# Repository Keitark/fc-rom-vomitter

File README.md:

# FC ROM Vomitter

[日本語](README_JA.md) · [Schematic PDF](docs/nescart-fc-schematic.pdf) · [Manufacturing release](manufacturing/rev-a-fc/)

**Upload an NROM homebrew ROM from a phone, load it into SRAM, and run it on a Japanese Famicom.** No EPROM programmer, cartridge swapping, or battery-backed memory.

The native 60-pin Famicom Rev A-FC is the primary design. A frozen 72-pin NES-001 predecessor is preserved under [`experimental/nes/`](experimental/nes/) for comparison and further development; it is not part of the FC manufacturing release. A separately isolated [ESP32-S3 two-bank Mapper-3 experiment](experimental/mapper3-esp32/) records the post-release bodge wiring, firmware, tests, and limited bench evidence without changing the stable NROM release.

## AI Expo: real hardware → reusable skills

**AIと実機を作る。その経験を、次の設計で使えるスキルにする。**
Build real hardware with AI—and reuse what the engineering process teaches us.

ROM Vomitter's engineering experience helped develop
[PCBA Design Skills](https://github.com/Keitark/pcba-design-skills).
The [ChatPCBA agent plugin](https://github.com/Keitark/chatpcba) packages eleven
specialist skills into an evidence-gated workflow for Codex. The original
cartridge predates the complete local ChatPCBA dashboard; it was not produced
by today's dashboard end to end.

実機開発の経験を再利用可能なスキルへ整理し、ChatPCBAで工程としてつなぎます。
公開物は実機資料・スキル・エージェントプラグインです。展示用ダッシュボードは
別のローカル実装であり、公開ホスティングサービスではありません。

Workflow: interview → requirements and applicable checks → circuit and sourcing
→ readable schematic → applicable simulation → placement/routing → fabrication
package → JLCPCB review. Engineering gates and human order/payment approval
remain distinct. See the validation limits below; a photograph is not a complete
bench qualification report.

## Actual board views

| Component / parts side | Artwork side |
|---|---|
|  |  |

> [!WARNING]
> Rev A-FC has a fabrication-complete design and build-tested firmware, but the assembled hardware has not completed bench validation. Do not insert an untested board into a Famicom. The 10 mm taller PCB also needs a custom shell; original cartridge-shell compatibility is not claimed.

## What it does

1. The ESP32-S3 creates a Wi-Fi access point and browser upload page.
2. An uploaded mapper-0 `.nes` image is CRC-checked and committed to one of two flash slots.
3. At power-up, the ESP32 isolates the console bus, copies PRG and CHR data into SRAM, and verifies every byte.
4. The bus changes to RUN ownership and the blue LED becomes solid.
5. Press the **Famicom console's red RESET button** to start the game.

For bench and unattended workflows, the firmware also supports [USB-C direct
upload and optional HTTPS cloud polling](docs/rom-delivery.md). All delivery
modes use the same validated atomic flash and SRAM-loading path.

Unlike the front-loader NES, the Famicom has no CIC lockout circuit. The cartridge therefore cannot automatically hold and release console reset; the explicit RESET press is part of the Rev A-FC user flow.

```mermaid
flowchart LR
    phone["Phone / laptop"] -->|"Wi-Fi upload"| esp["ESP32-S3"]
    esp --> flash["Two atomic flash slots"]
    flash -->|"CRC-verified copy"| sram["PRG + CHR SRAM"]
    esp -->|"LOAD / RUN ownership"| buffers["74LVC bus isolation"]
    sram --> buffers --> edge["60-pin Famicom edge"]
    edge --> console["Famicom CPU + PPU"]
    reset["Press console RESET"] -.-> console
```

## Hardware at a glance

| Area | Rev A-FC |
|---|---|
| Console | Japanese Famicom 60-pin cartridge slot |
| Supported image | iNES mapper 0 / NROM, 16 or 32 KiB PRG, 8 KiB CHR |
| Loader | ESP32-S3-WROOM-1-N8, SoftAP + browser upload |
| Game storage | Two atomic slots in ESP32 flash |
| Console memory | Two CY62128 128K × 8 SRAMs |
| Bus safety | 74LVC245 isolation with fail-safe LOAD/RUN defaults |
| PCB | 6 layers, 90.0 × 66.8 mm envelope, 1.2 mm, 60 gold fingers |
| Audio | Famicom sound loop through fitted 0 Ω R20 |
| Power/debug | Console 5 V plus USB-C bench power and native USB flashing |

The board keeps the standard-width tongue, connector datum, notches, centre slot, and 1.2 mm mating thickness. Only the edge opposite the fingers is extended by 10 mm for routing space.

## Project status

| Gate | Status | Evidence |
|---|---|---|
| Schematic ERC | **PASS** — 0 errors, 8 reviewed warnings | [`erc.json`](manufacturing/rev-a-fc/evidence/erc.json) |
| PCB connectivity | **PASS** — 0 raw opens | [`drc-classified.json`](manufacturing/rev-a-fc/evidence/drc-classified.json) |
| Classified DRC | **PASS** — 0 real errors | [`drc-classified.json`](manufacturing/rev-a-fc/evidence/drc-classified.json) |
| Layout policy | **PASS** — 0 failures | [`layout-check.txt`](manufacturing/rev-a-fc/evidence/layout-check.txt) |
| CPL registration | **PASS** — 79 fitted references, 0 unresolved | [`cpl-audit.txt`](manufacturing/rev-a-fc/evidence/cpl-audit.txt) |
| Firmware host tests/build | **PASS in preparation; continuously checked by CI** | [workflow](.github/workflows/validate.yml) |
| Electrical/mechanical bench validation | **PENDING** | [bring-up checklist](docs/bring-up.md) |

“0 opens” is not treated as completion by itself. The release also requires classified DRC, power continuity, reference-plane checks, silkscreen review, CPL registration, and visual inspection.

## Quick start for developers

### Firmware

Install [PlatformIO](https://platformio.org/), then:

```powershell
cd firmware
pio run -e esp32-s3
```

Host-test the iNES parser, CRC, and atomic-slot selection:

```powershell
cmake -S host_tests -B host_tests/build
cmake --build host_tests/build --config Release
ctest --test-dir host_tests/build -C Release --output-on-failure
```

The default development access-point password is `vomit-roms`. Change it through menuconfig before using the cartridge in a shared or public environment.

### Hardware

Open [`hardware/nescart-fc.kicad_pro`](hardware/nescart-fc.kicad_pro) in KiCad 10. The checked-in PCB is the exact revision used to create the public manufacturing package.

The schematic is generator-backed:

```powershell
python hardware/tools/gen_sch.py
```

Edit the netlist tables in `gen_sch.py`; do not hand-edit generated connectivity in the `.kicad_sch` files. See [hardware/README.md](hardware/README.md) before regenerating anything.

## Manufacturing release

[`manufacturing/rev-a-fc/`](manufacturing/rev-a-fc/) contains:

- revision-locked Gerber + drill ZIP;
- engineering and JLCPCB-format BOM/CPL files;
- CPL registration audit and assembly drawing;
- DRC/ERC/layout/silkscreen evidence;
- top and bottom manufacturing views and paste-stencil preview;
- a SHA-256 manifest checked in CI.

These files are published for review and reproducibility, **not as a recommendation to order an unvalidated board unchanged**. Read [manufacturing notes](docs/manufacturing.md) and the [bench bring-up gate](docs/bring-up.md) first.

## Experimental NES variant

[`experimental/nes/`](experimental/nes/) preserves the earlier 72-pin front-loader NES-001 design. It uses an ATtiny CIC clone to hold the console in reset while the ESP32 loads SRAM, which is materially different from the manual-reset FC flow. The snapshot passed its recorded schematic and PCB checks, but its assembly-placement gate and hardware validation are incomplete, so it is intentionally **not fabrication-ready**.

## Experimental Mapper 3 modification

[`experimental/mapper3-esp32/`](experimental/mapper3-esp32/) documents an
ESP32-S3-only, two-bank CNROM modification applied to one assembled Rev A-FC
board. It adds no new processor: a core-1 IRAM polling loop observes CPU D0 and
the existing decoded control signals, then drives CHR SRAM A13 through GPIO36.

Host tests, the ESP32 build, Mapper-0 regression, and one two-bank Mapper-3
target passed their recorded checks. Electrical margin, worst-case timing,
long-run Wi-Fi stress, and multi-board repeatability remain `USER_REVIEW`.
This is a reproducible experiment, not a revised manufacturing release.

## Repository map

```text
hardware/                 KiCad 10 release source, libraries, models and core generators
firmware/                 ESP-IDF / PlatformIO loader firmware and host tests
manufacturing/rev-a-fc/   sanitized Gerber, BOM, CPL, evidence and hashes
experimental/nes/          frozen 72-pin NES-001 design snapshot (not released)
experimental/mapper3-esp32/ post-release two-bank CNROM bodge and firmware
docs/                     architecture, bring-up, manufacturing and licensing notes
scripts/                  repository and release-integrity checks
```

## Documentation

- [Architecture and safety invariants](docs/architecture.md)
- [First-board bring-up](docs/bring-up.md)
- [Browser, USB-C and cloud ROM delivery](docs/rom-delivery.md)
- [Manufacturing and release interpretation](docs/manufacturing.md)
- [FC60 pin map](hardware/docs/pinout-fc.md)
- [Layout and electrical guidance](hardware/docs/layout-electrical-guidance.md)
- [Licensing and attribution](docs/licensing.md)
- [Japanese README / 日本語](README_JA.md)
- [Experimental ESP32-S3 Mapper 3 modification](experimental/mapper3-esp32/)

## License and credits

This is a dual-licensed repository. Software and original general documentation are MIT. KiCad hardware design files, manufacturing artifacts, and designated visual/model assets are CC BY-SA 4.0; see [the exact scope and attributions](docs/licensing.md).

Connector behavior and dimensional research reference the community-maintained [NESdev Wiki](https://www.nesdev.org/wiki/Cartridge_connector) and the [NES/Famicom cartridge dimensions project](https://github.com/Gumball2415/NES-Famicom-Cartridge-Dimensions). The SRAM STEP model is from KiCad Packages3D and retains its upstream license and exception.

Famicom and Nintendo are trademarks of Nintendo. This independent project is not affiliated with or endorsed by Nintendo. Use homebrew software you have the right to run.

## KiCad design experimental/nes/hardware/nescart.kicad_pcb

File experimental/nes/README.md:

# Experimental 72-pin NES-001 variant

[日本語](#日本語) · [Schematic PDF](docs/nescart-schematic.pdf)

This directory preserves the earlier front-loader NES-001 design as an experimental snapshot. It is included to make the architectural differences and design history reviewable; it is **not part of the Rev A-FC manufacturing release**.

## Why it differs from the Famicom board

The NES-001 contains a CIC lockout circuit. An ATtiny13A running a CIC-clone firmware keeps the console in reset while the ESP32-S3 owns the cartridge SRAM bus, then permits boot only after the ROM image has been copied and verified.

```mermaid
flowchart LR
    phone["Phone / laptop"] -->|"Wi-Fi upload"| esp["ESP32-S3"]
    esp -->|"load + verify"| sram["PRG + CHR SRAM"]
    cic["ATtiny13A CIC clone"] -->|"hold console reset"| nes["NES-001"]
    esp -->|"LOAD / RUN"| buffers["Bus isolation"]
    sram --> buffers --> edge["72-pin edge"] --> nes
```

## Frozen snapshot status

| Item | Recorded state |
|---|---|
| Target | Front-loader NES-001, 72-pin, NROM |
| PCB | 6 layers, 1.2 mm, CY62128 SRAM variant |
| ERC | 0 errors, 8 reviewed warnings |
| Raw disconnects | 0 |
| Classified DRC | 0 real errors |
| Layout policy | 0 failures |
| Assembly placement | **Incomplete** — browser-only placement edits existed and a clean regenerated CPL review was still required |
| Bench validation | **Not completed** |

The snapshot also records accepted prototype USB risks: 2.63 mm D+/D− length skew, one-via asymmetry, and no connector-side ESD device. Re-audit those choices before deriving hardware from this version.

The exact source hashes are recorded in [`evidence/snapshot.json`](evidence/snapshot.json). No Gerber/BOM/CPL manufacturing bundle is published for this experimental variant.

## License and attribution

The KiCad source, renders, and evidence in this directory are CC BY-SA 4.0. The cartridge edge footprint and board geometry derive from [emeargt/nes-cnrom](https://github.com/emeargt/nes-cnrom). See the repository [licensing details](../../docs/licensing.md).

## 日本語

ここにはフロントローダーNES-001用72ピン版の設計スナップショットを、実験資料として保存しています。ATtiny13AのCICクローンで本体をリセット状態に保ち、その間にESP32-S3がSRAMへROMを書き込む構成です。

回路図・未接続・分類済みDRC・レイアウト検査は記録上PASSですが、JLCPCB上の部品位置確認でブラウザ内だけの補正が残っており、元CPLへ反映して再生成・再アップロードする最終ゲートが未完了でした。実機検証も未完了です。このため、FC版とは分離し、**そのまま製造するためのリリースではありません**。

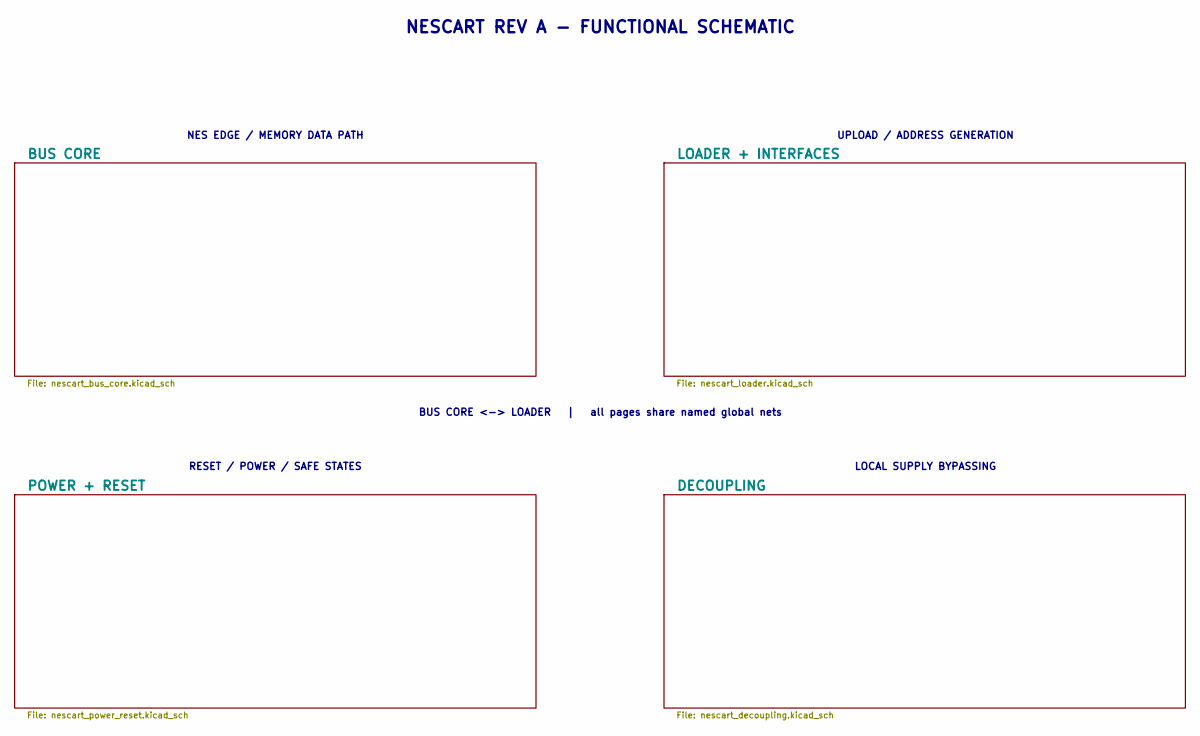
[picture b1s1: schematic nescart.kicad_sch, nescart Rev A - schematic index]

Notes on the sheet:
NESCART REV A - FUNCTIONAL SCHEMATIC
NES EDGE / MEMORY DATA PATH
UPLOAD / ADDRESS GENERATION
RESET / POWER / SAFE STATES
LOCAL SUPPLY BYPASSING
BUS CORE <-> LOADER | all pages share named global nets

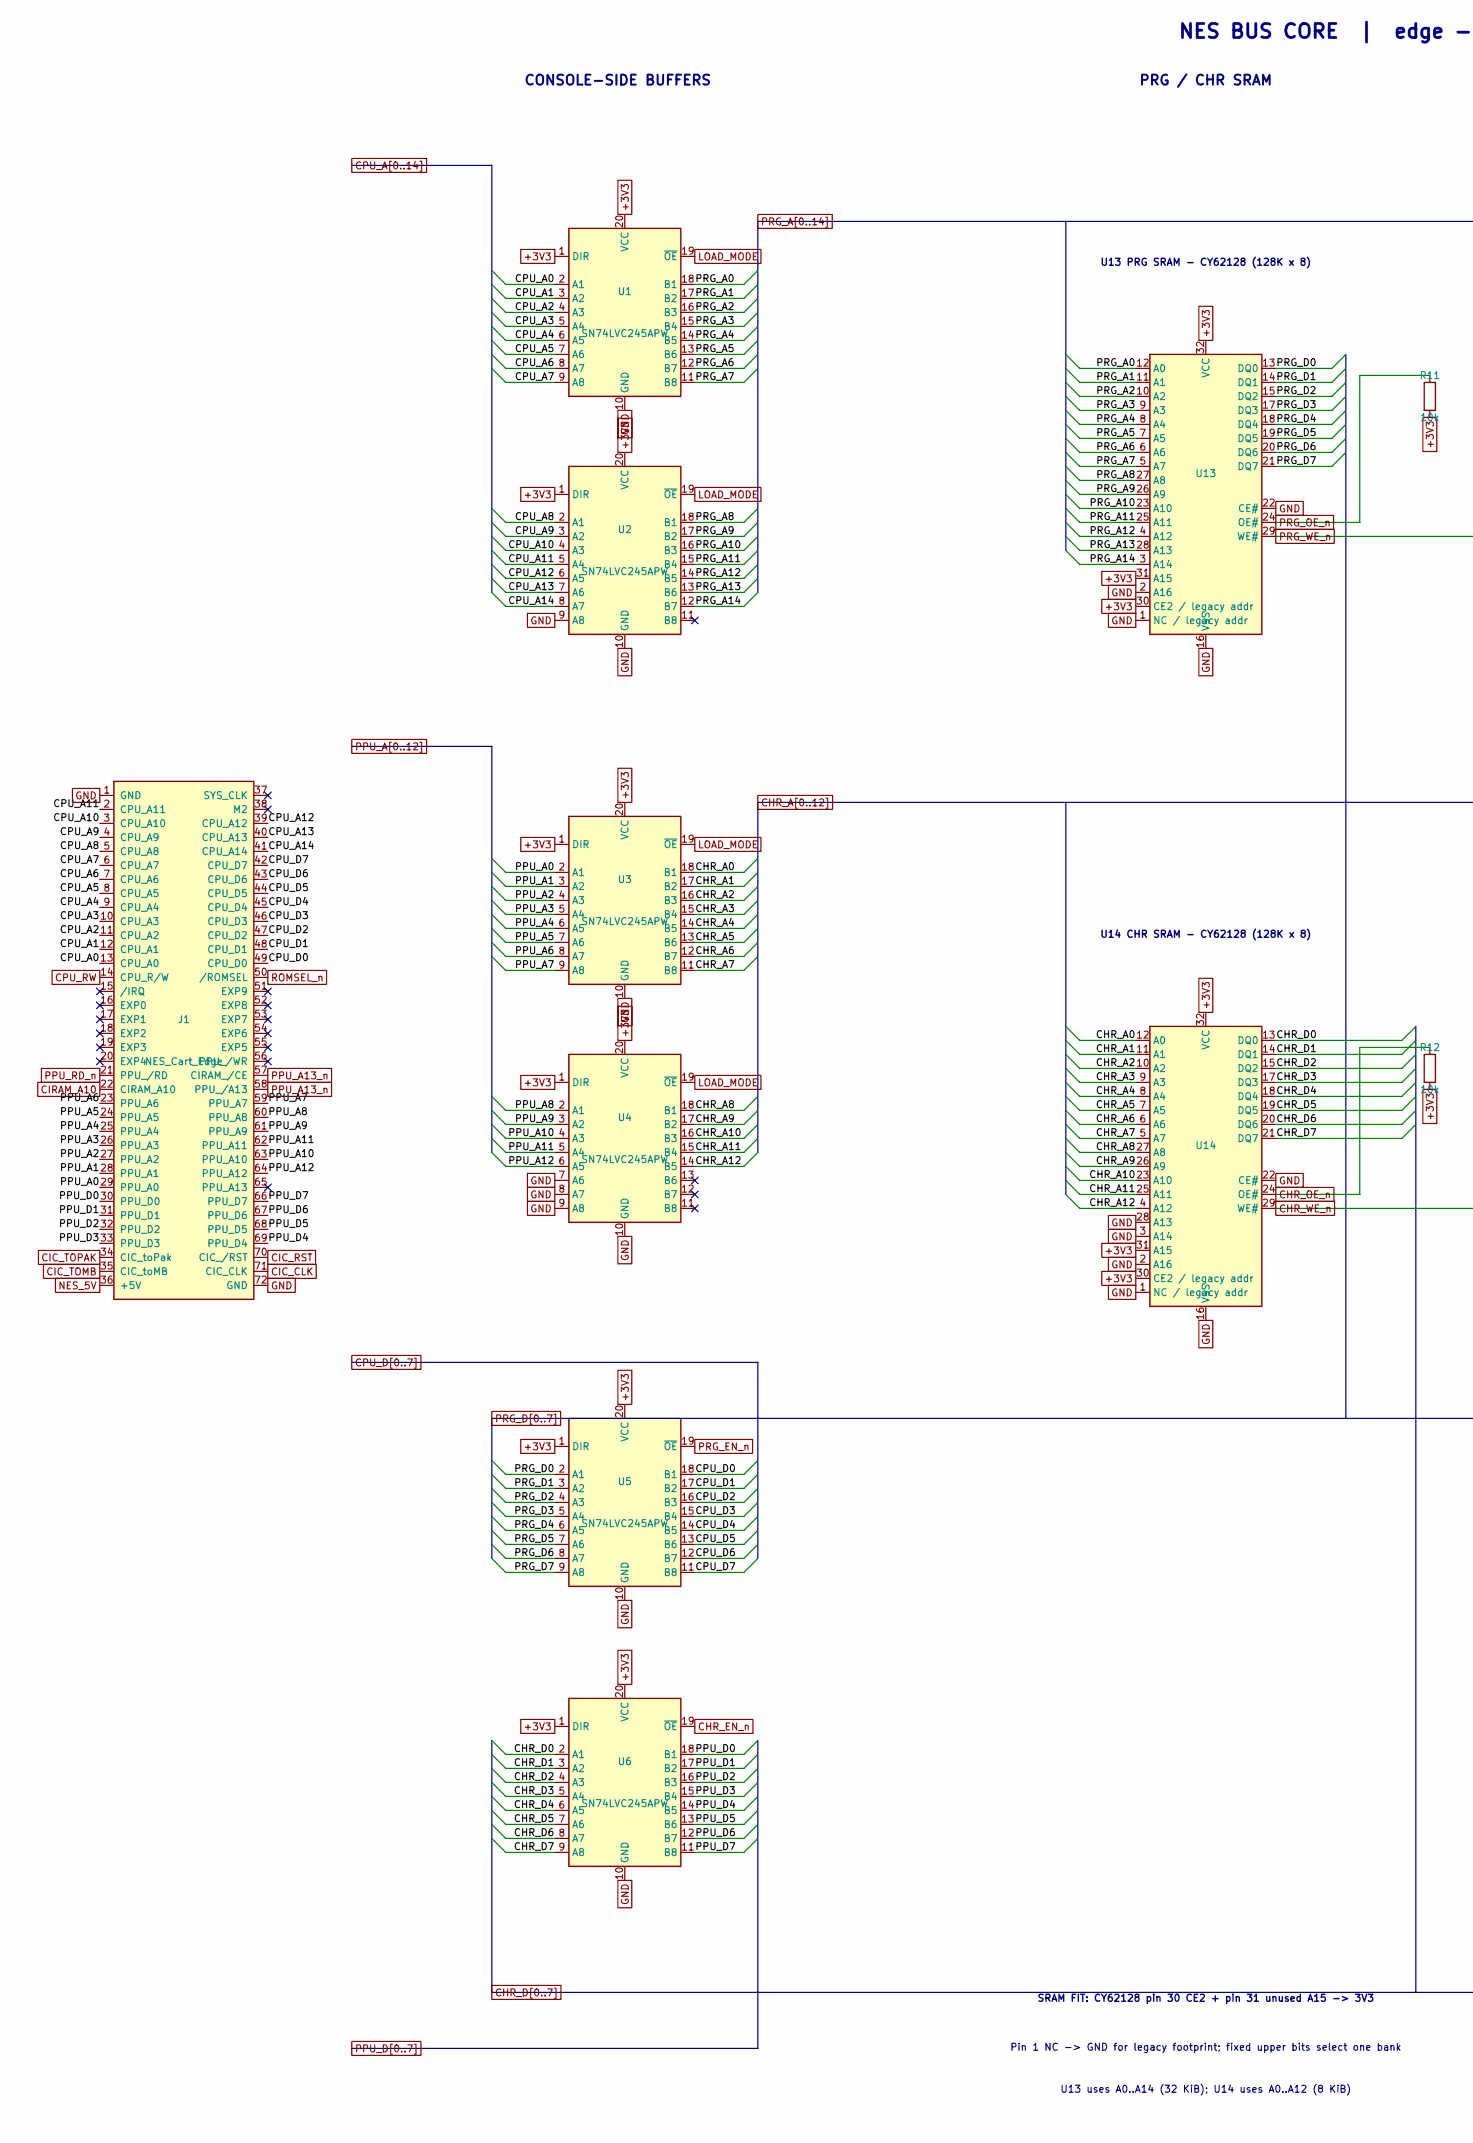
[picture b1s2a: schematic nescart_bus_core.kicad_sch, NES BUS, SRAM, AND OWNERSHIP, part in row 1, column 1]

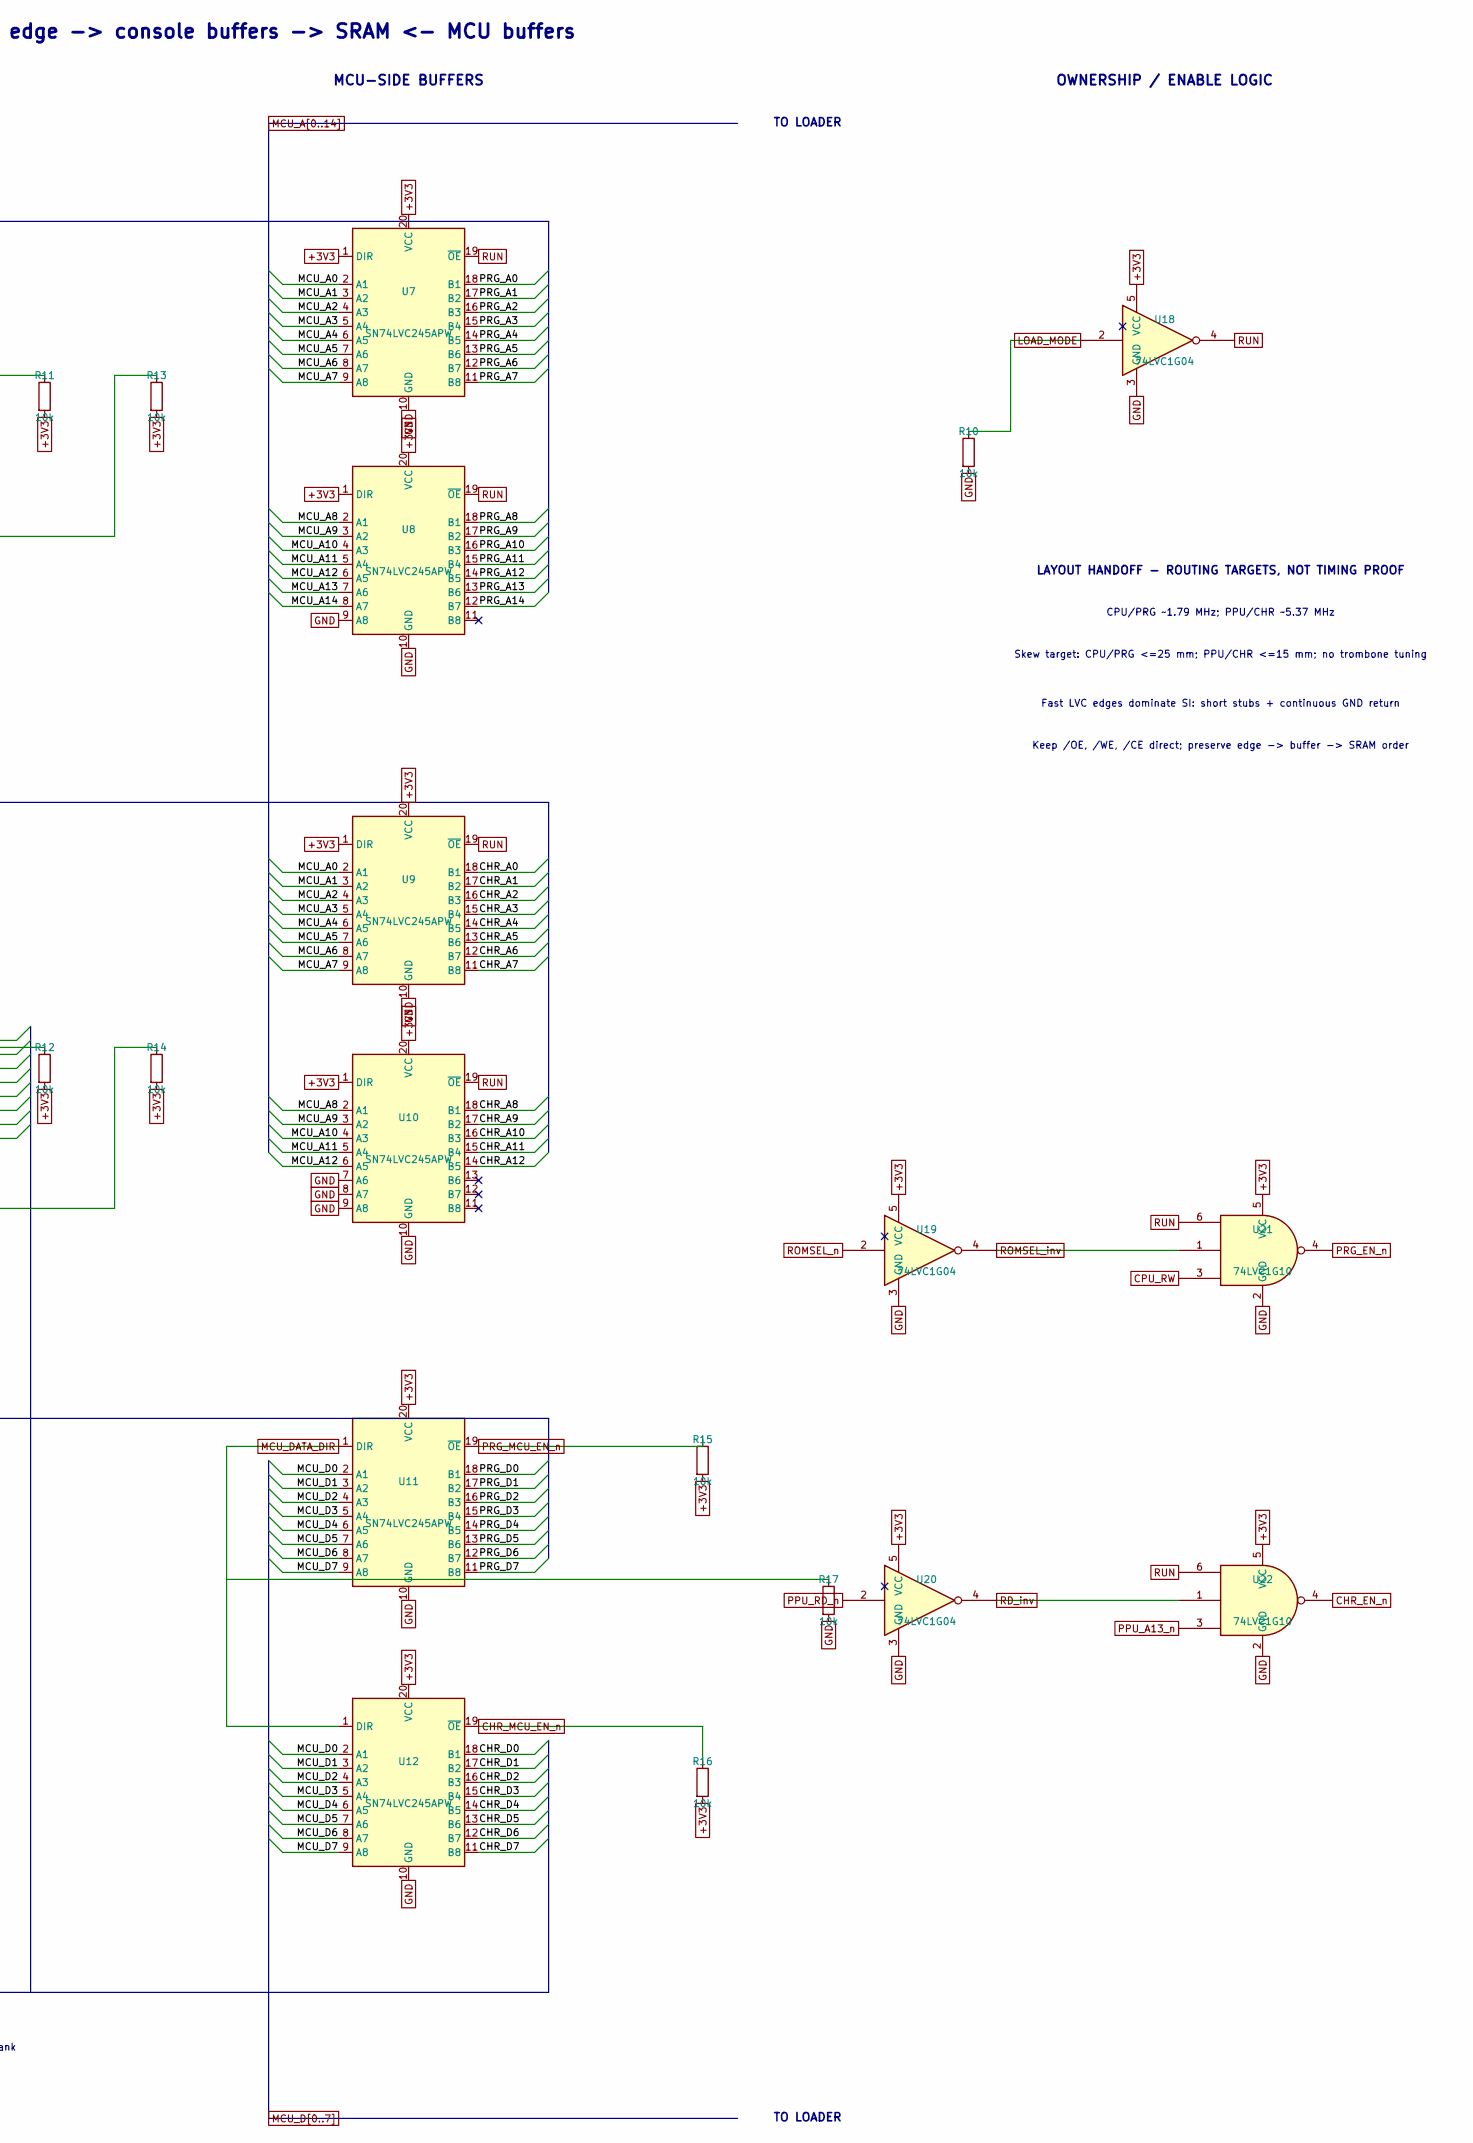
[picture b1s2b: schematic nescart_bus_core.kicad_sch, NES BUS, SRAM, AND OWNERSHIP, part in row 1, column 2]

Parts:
J1: NES_Cart_Edge; cartridge_edge_72
R10, R11, R12, R13, R14, R15, R16, R17: 10k; R_0603_1608Metric; MPN 0603 10k 1%
U1, U2, U3, U4, U5, U6, U7, U8, U9, U10, U11, U12: SN74LVC245APW; TSSOP-20_4.4x6.5mm_P0.65mm; MPN SN74LVC245APWR
U13, U14: CY62128EV30; SOP-32_11.305x20.495mm_P1.27mm; MPN CY62128EV30LL-45SXIT; LCSC C2840304
U18, U19, U20: 74LVC1G04; SOT-353_SC-70-5; MPN SN74LVC1G04DCKR
U21, U22: 74LVC1G10; SOT-363_SC-70-6; MPN SN74LVC1G10DCKR

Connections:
CHR_A0: U3.18 (B1), U9.18 (B1), U14.12 (A0)
CHR_A1: U3.17 (B2), U9.17 (B2), U14.11 (A1)
CHR_A2: U3.16 (B3), U9.16 (B3), U14.10 (A2)
CHR_A3: U3.15 (B4), U9.15 (B4), U14.9 (A3)
CHR_A4: U3.14 (B5), U9.14 (B5), U14.8 (A4)
CHR_A5: U3.13 (B6), U9.13 (B6), U14.7 (A5)
CHR_A6: U3.12 (B7), U9.12 (B7), U14.6 (A6)
CHR_A7: U3.11 (B8), U9.11 (B8), U14.5 (A7)
CHR_A8: U4.18 (B1), U10.18 (B1), U14.27 (A8)
CHR_A9: U4.17 (B2), U10.17 (B2), U14.26 (A9)
CHR_A10: U4.16 (B3), U10.16 (B3), U14.23 (A10)
CHR_A11: U4.15 (B4), U10.15 (B4), U14.25 (A11)
CHR_A12: U4.14 (B5), U10.14 (B5), U14.4 (A12)
CHR_D0: U6.2 (A1), U12.18 (B1), U14.13 (DQ0)
CHR_D1: U6.3 (A2), U12.17 (B2), U14.14 (DQ1)
CHR_D2: U6.4 (A3), U12.16 (B3), U14.15 (DQ2)
CHR_D3: U6.5 (A4), U12.15 (B4), U14.17 (DQ3)
CHR_D4: U6.6 (A5), U12.14 (B5), U14.18 (DQ4)
CHR_D5: U6.7 (A6), U12.13 (B6), U14.19 (DQ5)
CHR_D6: U6.8 (A7), U12.12 (B7), U14.20 (DQ6)
CHR_D7: U6.9 (A8), U12.11 (B8), U14.21 (DQ7)
CHR_EN_n: U6.19 (~OE), U22.4
CHR_MCU_EN_n: R16.1, U12.19 (~OE); also elsewhere on the board
CHR_OE_n: R12.1, U14.24 (OE#); also elsewhere on the board
CHR_WE_n: R14.1, U14.29 (WE#); also elsewhere on the board
CIC_CLK: J1.71 (CIC_CLK); also elsewhere on the board
CIC_RST: J1.70 (CIC_/RST); also elsewhere on the board
CIC_TOMB: J1.35 (CIC_toMB); also elsewhere on the board
CIC_TOPAK: J1.34 (CIC_toPak); also elsewhere on the board
CIRAM_A10: J1.22 (CIRAM_A10); also elsewhere on the board
CPU_A0: J1.13 (CPU_A0), U1.2 (A1)
CPU_A1: J1.12 (CPU_A1), U1.3 (A2)
CPU_A2: J1.11 (CPU_A2), U1.4 (A3)
CPU_A3: J1.10 (CPU_A3), U1.5 (A4)
CPU_A4: J1.9 (CPU_A4), U1.6 (A5)
CPU_A5: J1.8 (CPU_A5), U1.7 (A6)
CPU_A6: J1.7 (CPU_A6), U1.8 (A7)
CPU_A7: J1.6 (CPU_A7), U1.9 (A8)
CPU_A8: J1.5 (CPU_A8), U2.2 (A1)
CPU_A9: J1.4 (CPU_A9), U2.3 (A2)
CPU_A10: J1.3 (CPU_A10), U2.4 (A3)
CPU_A11: J1.2 (CPU_A11), U2.5 (A4)
CPU_A12: J1.39 (CPU_A12), U2.6 (A5)
CPU_A13: J1.40 (CPU_A13), U2.7 (A6)
CPU_A14: J1.41 (CPU_A14), U2.8 (A7)
CPU_D0: J1.49 (CPU_D0), U5.18 (B1)
CPU_D1: J1.48 (CPU_D1), U5.17 (B2)
CPU_D2: J1.47 (CPU_D2), U5.16 (B3)
CPU_D3: J1.46 (CPU_D3), U5.15 (B4)
CPU_D4: J1.45 (CPU_D4), U5.14 (B5)
CPU_D5: J1.44 (CPU_D5), U5.13 (B6)
CPU_D6: J1.43 (CPU_D6), U5.12 (B7)
CPU_D7: J1.42 (CPU_D7), U5.11 (B8)
CPU_RW: J1.14 (CPU_R/W), U21.3
GND: J1.1 (GND), J1.72 (GND), R10.2, R17.2, U1.10 (GND), U2.9 (A8), U2.10 (GND), U3.10 (GND), U4.7 (A6), U4.8 (A7), U4.9 (A8), U4.10 (GND), U5.10 (GND), U6.10 (GND), U7.10 (GND), U8.9 (A8), U8.10 (GND), U9.10 (GND), U10.7 (A6), U10.8 (A7), U10.9 (A8), U10.10 (GND), U11.10 (GND), U12.10 (GND), U13.1 (NC / legacy addr), U13.2 (A16), U13.16 (VSS), U13.22 (CE#), U14.1 (NC / legacy addr), U14.2 (A16), U14.3 (A14), U14.16 (VSS), U14.22 (CE#), U14.28 (A13), U18.3 (GND), U19.3 (GND), U20.3 (GND), U21.2 (GND), U22.2 (GND); also elsewhere on the board
LOAD_MODE: R10.1, U1.19 (~OE), U2.19 (~OE), U3.19 (~OE), U4.19 (~OE), U18.2; also elsewhere on the board
MCU_A0: U7.2 (A1), U9.2 (A1); also elsewhere on the board
MCU_A1: U7.3 (A2), U9.3 (A2); also elsewhere on the board
MCU_A2: U7.4 (A3), U9.4 (A3); also elsewhere on the board
MCU_A3: U7.5 (A4), U9.5 (A4); also elsewhere on the board
MCU_A4: U7.6 (A5), U9.6 (A5); also elsewhere on the board
MCU_A5: U7.7 (A6), U9.7 (A6); also elsewhere on the board
MCU_A6: U7.8 (A7), U9.8 (A7); also elsewhere on the board
MCU_A7: U7.9 (A8), U9.9 (A8); also elsewhere on the board
MCU_A8: U8.2 (A1), U10.2 (A1); also elsewhere on the board
MCU_A9: U8.3 (A2), U10.3 (A2); also elsewhere on the board
MCU_A10: U8.4 (A3), U10.4 (A3); also elsewhere on the board
MCU_A11: U8.5 (A4), U10.5 (A4); also elsewhere on the board
MCU_A12: U8.6 (A5), U10.6 (A5); also elsewhere on the board
MCU_A13: U8.7 (A6); also elsewhere on the board
MCU_A14: U8.8 (A7); also elsewhere on the board
MCU_D0: U11.2 (A1), U12.2 (A1); also elsewhere on the board
MCU_D1: U11.3 (A2), U12.3 (A2); also elsewhere on the board
MCU_D2: U11.4 (A3), U12.4 (A3); also elsewhere on the board
MCU_D3: U11.5 (A4), U12.5 (A4); also elsewhere on the board
MCU_D4: U11.6 (A5), U12.6 (A5); also elsewhere on the board
MCU_D5: U11.7 (A6), U12.7 (A6); also elsewhere on the board
MCU_D6: U11.8 (A7), U12.8 (A7); also elsewhere on the board
MCU_D7: U11.9 (A8), U12.9 (A8); also elsewhere on the board
MCU_DATA_DIR: R17.1, U11.1 (DIR), U12.1 (DIR); also elsewhere on the board
NES_5V: J1.36 (+5V); also elsewhere on the board
PPU_A0: J1.29 (PPU_A0), U3.2 (A1)
PPU_A1: J1.28 (PPU_A1), U3.3 (A2)
PPU_A2: J1.27 (PPU_A2), U3.4 (A3)
PPU_A3: J1.26 (PPU_A3), U3.5 (A4)
PPU_A4: J1.25 (PPU_A4), U3.6 (A5)
PPU_A5: J1.24 (PPU_A5), U3.7 (A6)
PPU_A6: J1.23 (PPU_A6), U3.8 (A7)
PPU_A7: J1.59 (PPU_A7), U3.9 (A8)
PPU_A8: J1.60 (PPU_A8), U4.2 (A1)
PPU_A9: J1.61 (PPU_A9), U4.3 (A2)
PPU_A10: J1.63 (PPU_A10), U4.4 (A3); also elsewhere on the board
PPU_A11: J1.62 (PPU_A11), U4.5 (A4); also elsewhere on the board
PPU_A12: J1.64 (PPU_A12), U4.6 (A5)
PPU_A13_n: J1.57 (CIRAM_/CE), J1.58 (PPU_/A13), U22.3
PPU_D0: J1.30 (PPU_D0), U6.18 (B1)
PPU_D1: J1.31 (PPU_D1), U6.17 (B2)
PPU_D2: J1.32 (PPU_D2), U6.16 (B3)
PPU_D3: J1.33 (PPU_D3), U6.15 (B4)
PPU_D4: J1.69 (PPU_D4), U6.14 (B5)
PPU_D5: J1.68 (PPU_D5), U6.13 (B6)
PPU_D6: J1.67 (PPU_D6), U6.12 (B7)
PPU_D7: J1.66 (PPU_D7), U6.11 (B8)
PPU_RD_n: J1.21 (PPU_/RD), U20.2
PRG_A0: U1.18 (B1), U7.18 (B1), U13.12 (A0)
PRG_A1: U1.17 (B2), U7.17 (B2), U13.11 (A1)
PRG_A2: U1.16 (B3), U7.16 (B3), U13.10 (A2)
PRG_A3: U1.15 (B4), U7.15 (B4), U13.9 (A3)
PRG_A4: U1.14 (B5), U7.14 (B5), U13.8 (A4)
PRG_A5: U1.13 (B6), U7.13 (B6), U13.7 (A5)
PRG_A6: U1.12 (B7), U7.12 (B7), U13.6 (A6)
PRG_A7: U1.11 (B8), U7.11 (B8), U13.5 (A7)
PRG_A8: U2.18 (B1), U8.18 (B1), U13.27 (A8)
PRG_A9: U2.17 (B2), U8.17 (B2), U13.26 (A9)
PRG_A10: U2.16 (B3), U8.16 (B3), U13.23 (A10)
PRG_A11: U2.15 (B4), U8.15 (B4), U13.25 (A11)
PRG_A12: U2.14 (B5), U8.14 (B5), U13.4 (A12)
PRG_A13: U2.13 (B6), U8.13 (B6), U13.28 (A13)
PRG_A14: U2.12 (B7), U8.12 (B7), U13.3 (A14)
PRG_D0: U5.2 (A1), U11.18 (B1), U13.13 (DQ0)
PRG_D1: U5.3 (A2), U11.17 (B2), U13.14 (DQ1)
PRG_D2: U5.4 (A3), U11.16 (B3), U13.15 (DQ2)
PRG_D3: U5.5 (A4), U11.15 (B4), U13.17 (DQ3)
PRG_D4: U5.6 (A5), U11.14 (B5), U13.18 (DQ4)
PRG_D5: U5.7 (A6), U11.13 (B6), U13.19 (DQ5)
PRG_D6: U5.8 (A7), U11.12 (B7), U13.20 (DQ6)
PRG_D7: U5.9 (A8), U11.11 (B8), U13.21 (DQ7)
PRG_EN_n: U5.19 (~OE), U21.4
PRG_MCU_EN_n: R15.1, U11.19 (~OE); also elsewhere on the board
PRG_OE_n: R11.1, U13.24 (OE#); also elsewhere on the board
PRG_WE_n: R13.1, U13.29 (WE#); also elsewhere on the board
RD_inv: U20.4, U22.1
ROMSEL_inv: U19.4, U21.1
ROMSEL_n: J1.50 (/ROMSEL), U19.2
RUN: U7.19 (~OE), U8.19 (~OE), U9.19 (~OE), U10.19 (~OE), U18.4, U21.6, U22.6

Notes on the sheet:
NES BUS CORE | edge -> console buffers -> SRAM <- MCU buffers
CONSOLE-SIDE BUFFERS
PRG / CHR SRAM
U13 PRG SRAM - CY62128 (128K x 8)
U14 CHR SRAM - CY62128 (128K x 8)
MCU-SIDE BUFFERS
OWNERSHIP / ENABLE LOGIC
TO LOADER
LAYOUT HANDOFF - ROUTING TARGETS, NOT TIMING PROOF
CPU/PRG ~1.79 MHz; PPU/CHR ~5.37 MHz
Skew target: CPU/PRG <=25 mm; PPU/CHR <=15 mm; no trombone tuning
Fast LVC edges dominate SI: short stubs + continuous GND return
Keep /OE, /WE, /CE direct; preserve edge -> buffer -> SRAM order
SRAM FIT: CY62128 pin 30 CE2 + pin 31 unused A15 -> 3V3
Pin 1 NC -> GND for legacy footprint; fixed upper bits select one bank
U13 uses A0..A14 (32 KiB); U14 uses A0..A12 (8 KiB)

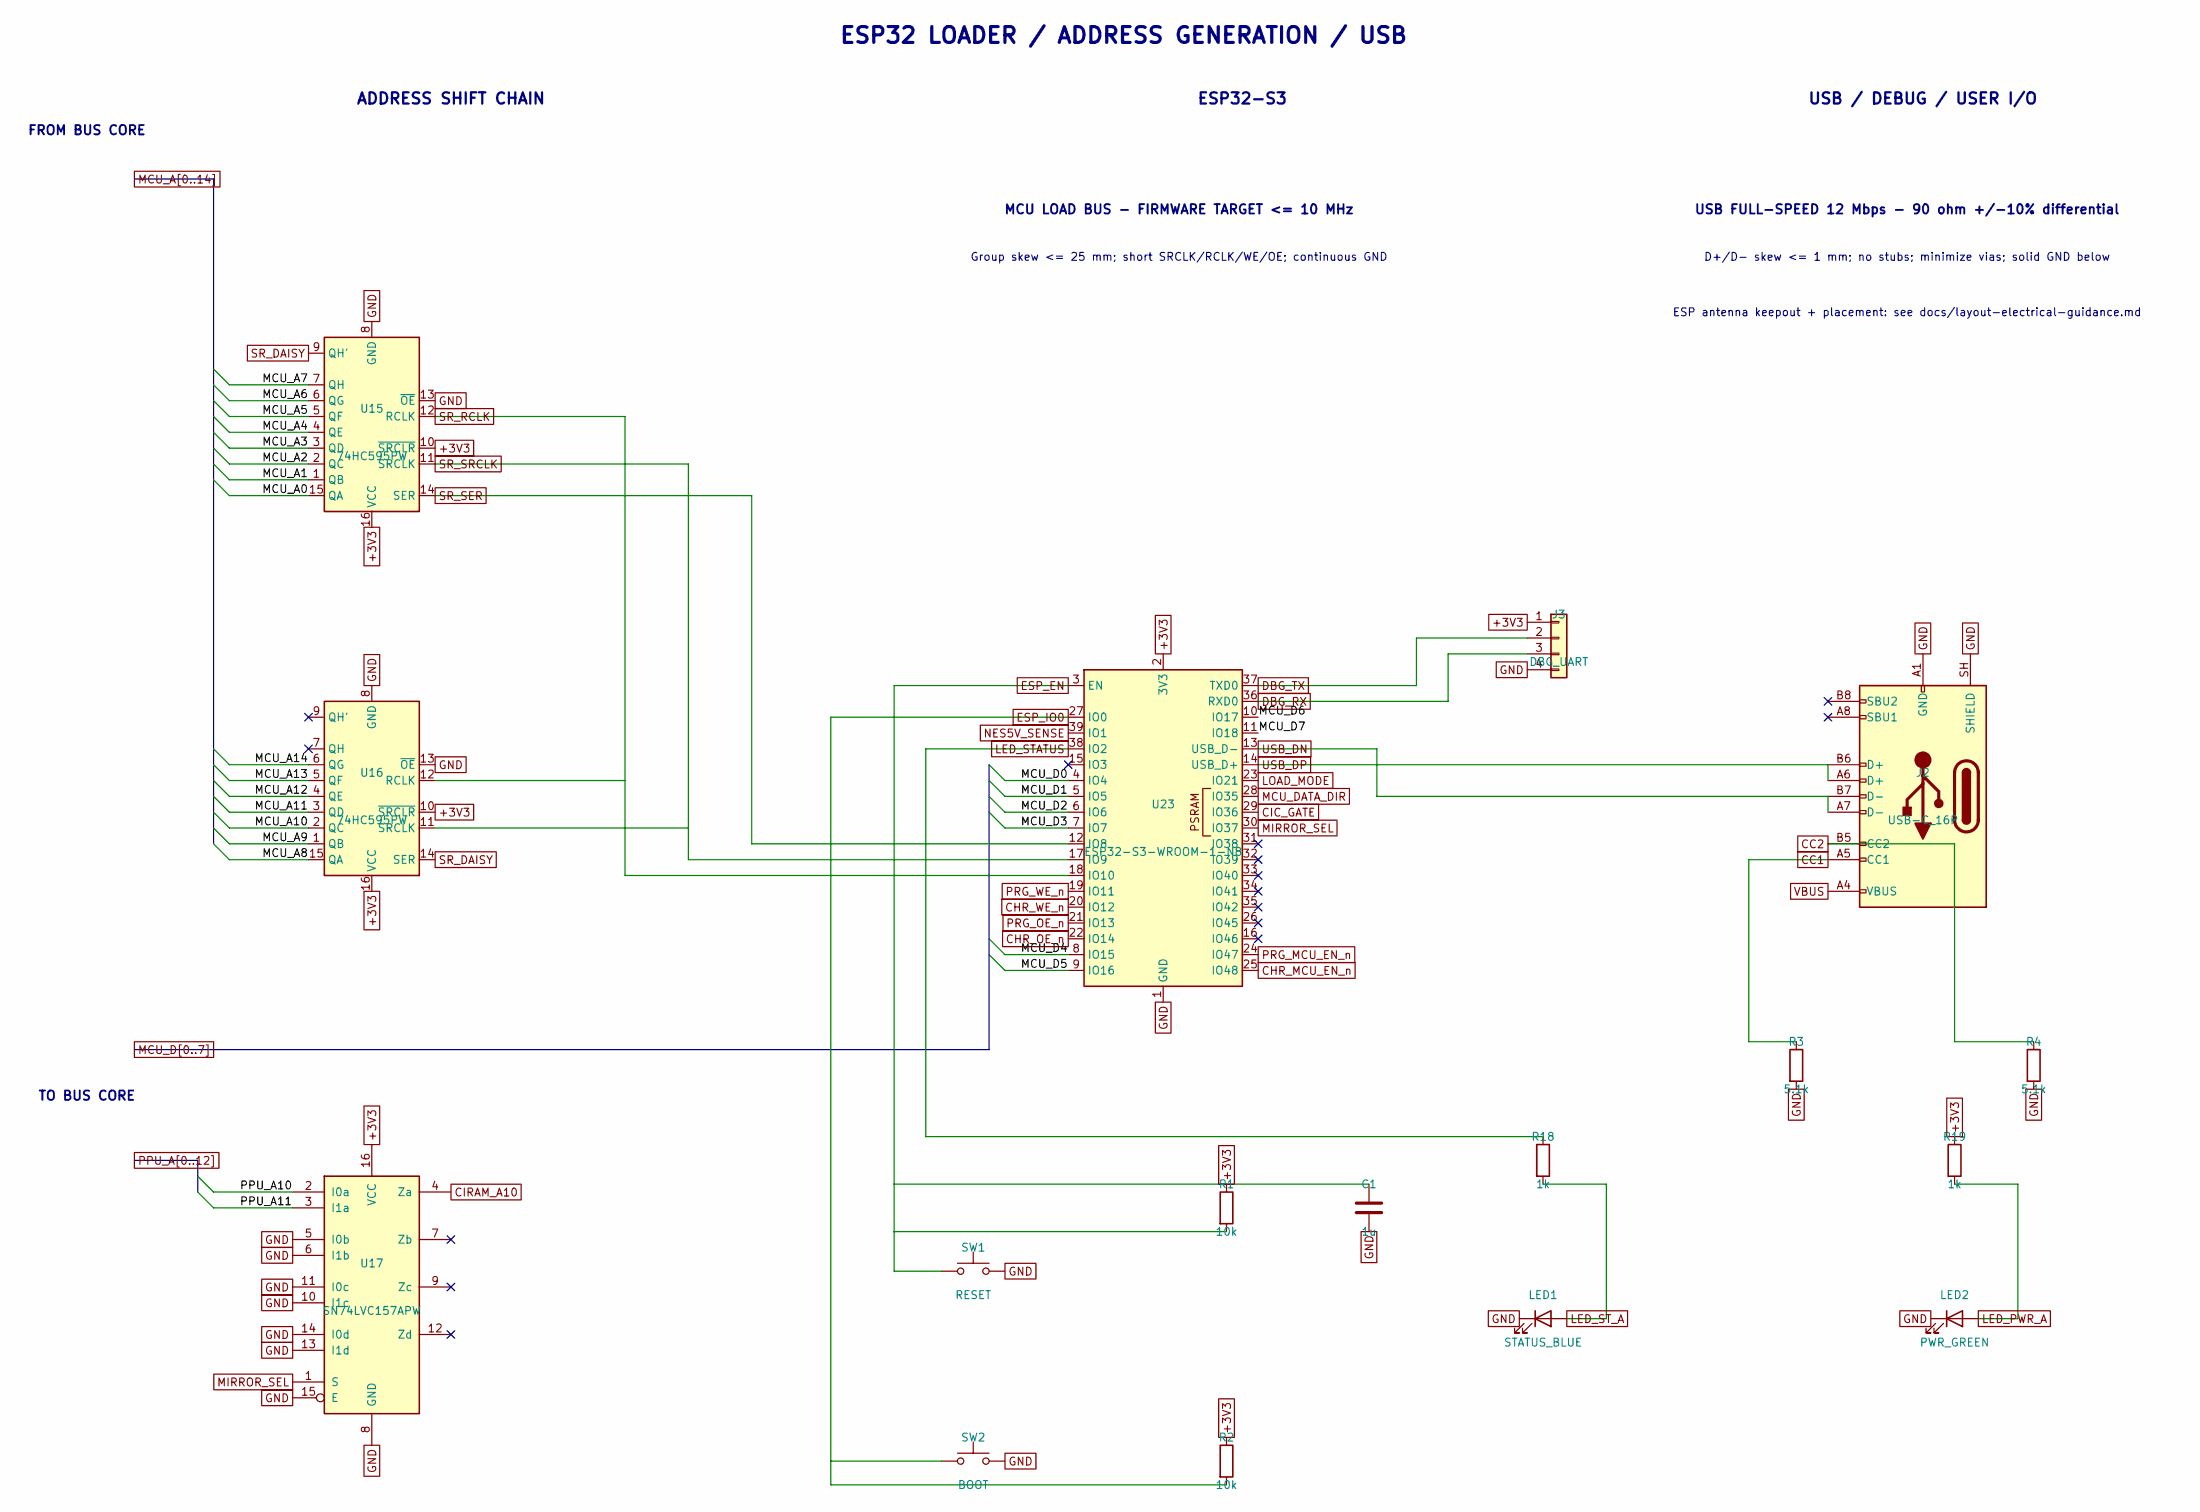
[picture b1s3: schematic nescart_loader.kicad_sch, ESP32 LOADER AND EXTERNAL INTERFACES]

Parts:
C1: 1u; C_0603_1608Metric; MPN 1u X7R
J2: USB-C_16P; USB_C_Receptacle_HRO_TYPE-C-31-M-12; MPN HRO TYPE-C-31-M-12
J3: DBG_UART; PinHeader_1x04_P2.54mm_Vertical; MPN PinHeader 1x4
LED1: STATUS_BLUE; LED_0603_1608Metric; MPN 0603 LED
LED2: PWR_GREEN; LED_0603_1608Metric; MPN 0603 LED
R1, R2: 10k; R_0603_1608Metric; MPN 0603 10k 1%
R3, R4: 5.1k; R_0603_1608Metric; MPN 0603 5.1k 1%
R18, R19: 1k; R_0603_1608Metric; MPN 0603 1k 1%
SW1: RESET; SW_SPST_B3U-1000P; MPN B3U-1000P
SW2: BOOT; SW_SPST_B3U-1000P; MPN B3U-1000P
U15, U16: 74HC595PW; TSSOP-16_4.4x5mm_P0.65mm; MPN SN74HC595PWR
U17: SN74LVC157APW; TSSOP-16_4.4x5mm_P0.65mm; MPN SN74LVC157APWR
U23: ESP32-S3-WROOM-1-N8; ESP32-S3-WROOM-1; MPN ESP32-S3-WROOM-1-N8

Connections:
CC1: J2.A5 (CC1), R3.1
CC2: J2.B5 (CC2), R4.1
CHR_MCU_EN_n: U23.25 (IO48); also elsewhere on the board
CHR_OE_n: U23.22 (IO14); also elsewhere on the board
CHR_WE_n: U23.20 (IO12); also elsewhere on the board
CIC_GATE: U23.29 (IO36); also elsewhere on the board
CIRAM_A10: U17.4 (Za); also elsewhere on the board
DBG_RX: J3.3, U23.36 (RXD0)
DBG_TX: J3.2, U23.37 (TXD0)
ESP_IO0: R2.2, SW2.1, U23.27 (IO0)
GND: C1.2, J2.A1 (GND), J2.A12 (GND), J2.B1 (GND), J2.B12 (GND), J2.SH (SHIELD), J3.4, LED1.1 (K), LED2.1 (K), R3.2, R4.2, SW1.2, SW2.2, U15.8 (GND), U15.13 (~OE), U16.8 (GND), U16.13 (~OE), U17.5 (I0b), U17.6 (I1b), U17.8 (GND), U17.10 (I1c), U17.11 (I0c), U17.13 (I1d), U17.14 (I0d), U17.15 (E), U23.1 (GND), U23.40 (GND), U23.41 (GND); also elsewhere on the board
LED_PWR_A: LED2.2 (A), R19.2
LED_STATUS: R18.1, U23.38 (IO2)
LED_ST_A: LED1.2 (A), R18.2
LOAD_MODE: U23.23 (IO21); also elsewhere on the board
MCU_A0: U15.15 (QA); also elsewhere on the board
MCU_A1: U15.1 (QB); also elsewhere on the board
MCU_A2: U15.2 (QC); also elsewhere on the board
MCU_A3: U15.3 (QD); also elsewhere on the board
MCU_A4: U15.4 (QE); also elsewhere on the board
MCU_A5: U15.5 (QF); also elsewhere on the board
MCU_A6: U15.6 (QG); also elsewhere on the board
MCU_A7: U15.7 (QH); also elsewhere on the board
MCU_A8: U16.15 (QA); also elsewhere on the board
MCU_A9: U16.1 (QB); also elsewhere on the board
MCU_A10: U16.2 (QC); also elsewhere on the board
MCU_A11: U16.3 (QD); also elsewhere on the board
MCU_A12: U16.4 (QE); also elsewhere on the board
MCU_A13: U16.5 (QF); also elsewhere on the board
MCU_A14: U16.6 (QG); also elsewhere on the board
MCU_D0: U23.4 (IO4); also elsewhere on the board
MCU_D1: U23.5 (IO5); also elsewhere on the board
MCU_D2: U23.6 (IO6); also elsewhere on the board
MCU_D3: U23.7 (IO7); also elsewhere on the board
MCU_D4: U23.8 (IO15); also elsewhere on the board
MCU_D5: U23.9 (IO16); also elsewhere on the board
MCU_D6: U23.10 (IO17); also elsewhere on the board
MCU_D7: U23.11 (IO18); also elsewhere on the board
MCU_DATA_DIR: U23.28 (IO35); also elsewhere on the board
MIRROR_SEL: U17.1 (S), U23.30 (IO37)
NES5V_SENSE: U23.39 (IO1); also elsewhere on the board
PPU_A10: U17.2 (I0a); also elsewhere on the board
PPU_A11: U17.3 (I1a); also elsewhere on the board
PRG_MCU_EN_n: U23.24 (IO47); also elsewhere on the board
PRG_OE_n: U23.21 (IO13); also elsewhere on the board
PRG_WE_n: U23.19 (IO11); also elsewhere on the board
SR_DAISY: U15.9 (QH'), U16.14 (SER)
SR_RCLK: U15.12 (RCLK), U16.12 (RCLK), U23.18 (IO10)
SR_SER: U15.14 (SER), U23.12 (IO8)
SR_SRCLK: U15.11 (SRCLK), U16.11 (SRCLK), U23.17 (IO9)
USB_DN: J2.A7 (D-), J2.B7 (D-), U23.13 (USB_D-)
USB_DP: J2.A6 (D+), J2.B6 (D+), U23.14 (USB_D+)
VBUS: J2.A4 (VBUS), J2.A9 (VBUS), J2.B4 (VBUS), J2.B9 (VBUS); also elsewhere on the board

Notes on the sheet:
ESP32 LOADER / ADDRESS GENERATION / USB
ADDRESS SHIFT CHAIN
ESP32-S3
USB / DEBUG / USER I/O
FROM BUS CORE
TO BUS CORE
MCU LOAD BUS - FIRMWARE TARGET <= 10 MHz
Group skew <= 25 mm; short SRCLK/RCLK/WE/OE; continuous GND
USB FULL-SPEED 12 Mbps - 90 ohm +/-10% differential
D+/D- skew <= 1 mm; no stubs; minimize vias; solid GND below
ESP antenna keepout + placement: see docs/layout-electrical-guidance.md

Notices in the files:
README.md:
Code license: MIT
Hardware license: CC BY-SA 4.0
